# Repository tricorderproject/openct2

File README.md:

openct2
======

Open Source Computed Tomography (CT) Scanner v2 <br>
http://www.tricorderproject.org/openct <br>
Copyright (C) 2015  Peter Jansen and the Tricorder project <br>
peter@tricorderproject.org <br>
Project Build Logs: https://hackaday.io/project/5946-openct2 <br>

# Introduction

The Open Source Computed Tomography (CT) Scanner project aims to move towards creating an inexpensive and open desktop computed tomography scanner for academic and educational purposes.  The most common form of computed tomography is radiographic using x-rays or gamma rays, although it is my hope that this project can serve as a general platform for other kinds of tomographic research with other, safer wavelengths. 

This project is intended for use with radioisotope "check" sources that are many orders of magnitude less intense than sources in a commercial or medical radiographic setups.  This means that even very low resolution images will take hours of measurement and integration time to assemble, and the resolution and signal to noise ratio of a scan are largely a function of time (and patience).  Much of the spirit of this project is to move towards creating better scans through the use of clever signal processing techniques or wavelengths that can be more efficiently detected, rather than increasing source intensity. 

# Open Source

This project is open hardware and is released under various open licenses.  Please see LICENSES.TXT for details.

For potential contributors, a list of suggested contributions and next steps can be found in TODO.TXT .

# Warning

This project has a variety of dangers associated with it, including (without limitation) its assembly and use.  This generally includes the typical hazards involved with assembling, testing, and using electronics projects, CNC projects, as well as using hand tools, power tools, and CNC manufacturing tools such as laser cutters or CNC routers.  This is not a first project in any of these areas, and one should be well experienced and comfortable in all aspects of this project's design, assembly, and use. 

In addition, for radiography this project makes use of a low intensity sealed radioactive radioisotope source.  You should be experienced and extremely comfortable with handling and using radioactive sources, understanding the potential dangers (and how to minimize them), as well as any local laws or regulations regarding such material.  Having advanced training in medical imaging, radiography, and/or radiation biophysics is highly recommended.  

In no case should any living thing be placed inside of or be scanned by the device. 

**DISCLAIMER OF WARRANTIES AND LIMITATION OF LIABILITY.**

UNLESS OTHERWISE SEPARATELY UNDERTAKEN BY THE LICENSOR, TO THE EXTENT POSSIBLE, THE LICENSOR OFFERS THE LICENSED MATERIAL AS-IS AND AS-AVAILABLE, AND MAKES NO REPRESENTATIONS OR WARRANTIES OF ANY KIND CONCERNING THE LICENSED MATERIAL, WHETHER EXPRESS, IMPLIED, STATUTORY, OR OTHER. THIS INCLUDES, WITHOUT LIMITATION, WARRANTIES OF TITLE, MERCHANTABILITY, FITNESS FOR A PARTICULAR PURPOSE, NON-INFRINGEMENT, ABSENCE OF LATENT OR OTHER DEFECTS, ACCURACY, OR THE PRESENCE OR ABSENCE OF ERRORS, WHETHER OR NOT KNOWN OR DISCOVERABLE. WHERE DISCLAIMERS OF WARRANTIES ARE NOT ALLOWED IN FULL OR IN PART, THIS DISCLAIMER MAY NOT APPLY TO YOU.

TO THE EXTENT POSSIBLE, IN NO EVENT WILL THE LICENSOR BE LIABLE TO YOU ON ANY LEGAL THEORY (INCLUDING, WITHOUT LIMITATION, NEGLIGENCE) OR OTHERWISE FOR ANY DIRECT, SPECIAL, INDIRECT, INCIDENTAL, CONSEQUENTIAL, PUNITIVE, EXEMPLARY, OR OTHER LOSSES, COSTS, EXPENSES, OR DAMAGES ARISING OUT OF THIS PUBLIC LICENSE OR USE OF THE LICENSED MATERIAL, EVEN IF THE LICENSOR HAS BEEN ADVISED OF THE POSSIBILITY OF SUCH LOSSES, COSTS, EXPENSES, OR DAMAGES. WHERE A LIMITATION OF LIABILITY IS NOT ALLOWED IN FULL OR IN PART, THIS LIMITATION MAY NOT APPLY TO YOU.

THE DISCLAIMER OF WARRANTIES AND LIMITATION OF LIABILITY PROVIDED ABOVE SHALL BE INTERPRETED IN A MANNER THAT, TO THE EXTENT POSSIBLE, MOST CLOSELY APPROXIMATES AN ABSOLUTE DISCLAIMER AND WAIVER OF ALL LIABILITY.

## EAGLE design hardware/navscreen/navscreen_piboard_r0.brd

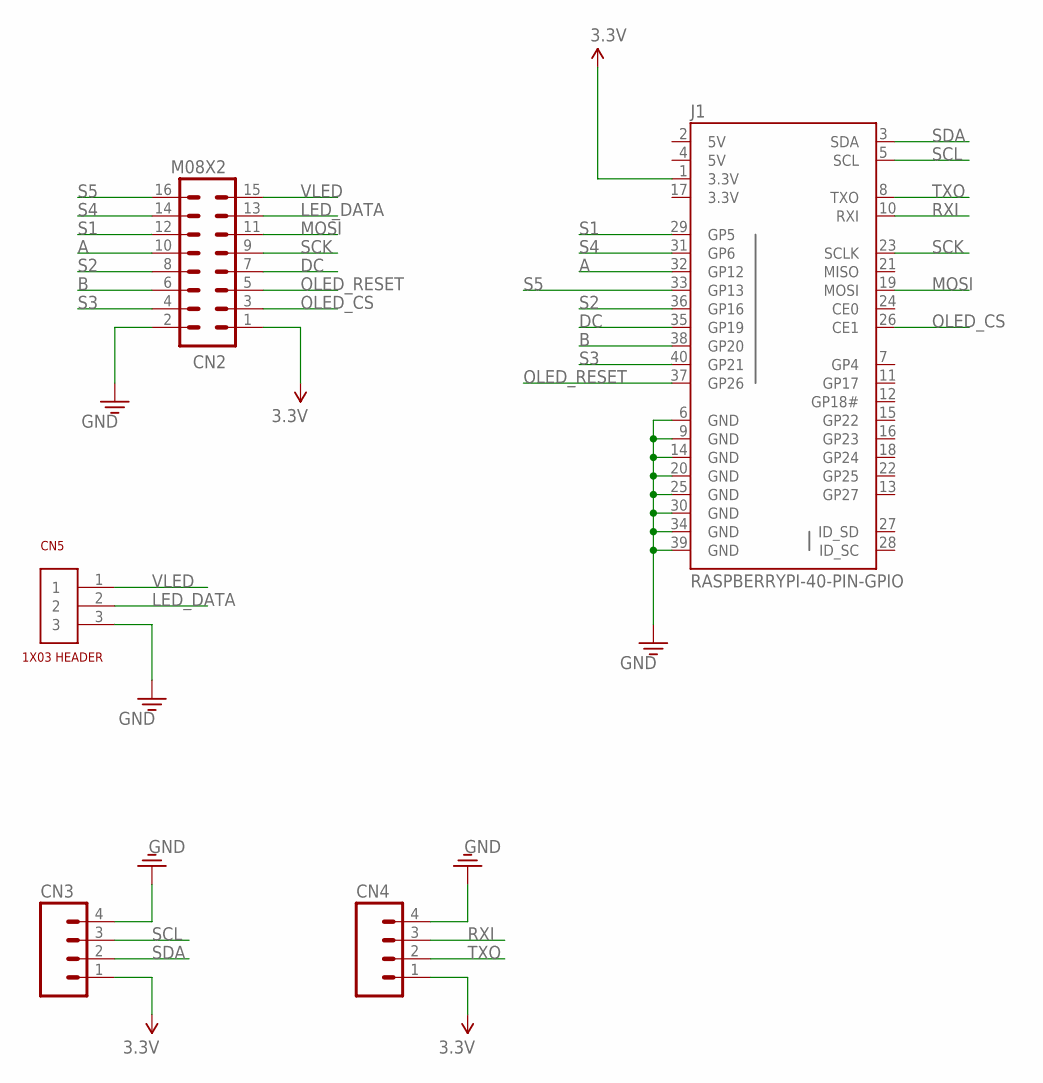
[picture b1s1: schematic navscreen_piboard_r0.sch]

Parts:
CN2: M08X2; 2X8
CN3, CN4: M04PTH; 1X04
CN5: 1X03
J1: RASPBERRYPI-40-PIN-GPIO; 2X20-SHROUDED

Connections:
3.3V: CN2.1, CN3.1, CN4.1, J1.1 (3.3V), J1.17 (3.3V)
A: CN2.10, J1.32 (GP12)
B: CN2.6, J1.38 (GP20)
DC: CN2.7, J1.35 (GP19)
GND: CN2.2, CN3.4, CN4.4, CN5.3, J1.6 (GND), J1.9 (GND), J1.14 (GND), J1.20 (GND), J1.25 (GND), J1.30 (GND), J1.34 (GND), J1.39 (GND)
LED_DATA: CN2.13, CN5.2
MOSI: CN2.11, J1.19 (MOSI)
OLED_CS: CN2.3, J1.26 (CE1)
OLED_RESET: CN2.5, J1.37 (GP26)
RXI: CN4.3, J1.10 (RXI)
S1: CN2.12, J1.29 (GP5)
S2: CN2.8, J1.36 (GP16)
S3: CN2.4, J1.40 (GP21)
S4: CN2.14, J1.31 (GP6)
S5: CN2.16, J1.33 (GP13)
SCK: CN2.9, J1.23 (SCLK)
SCL: CN3.3, J1.5 (SCL)
SDA: CN3.2, J1.3 (SDA)
TXO: CN4.2, J1.8 (TXO)
VLED: CN2.15, CN5.1, J1.2 (5V), J1.4 (5V)

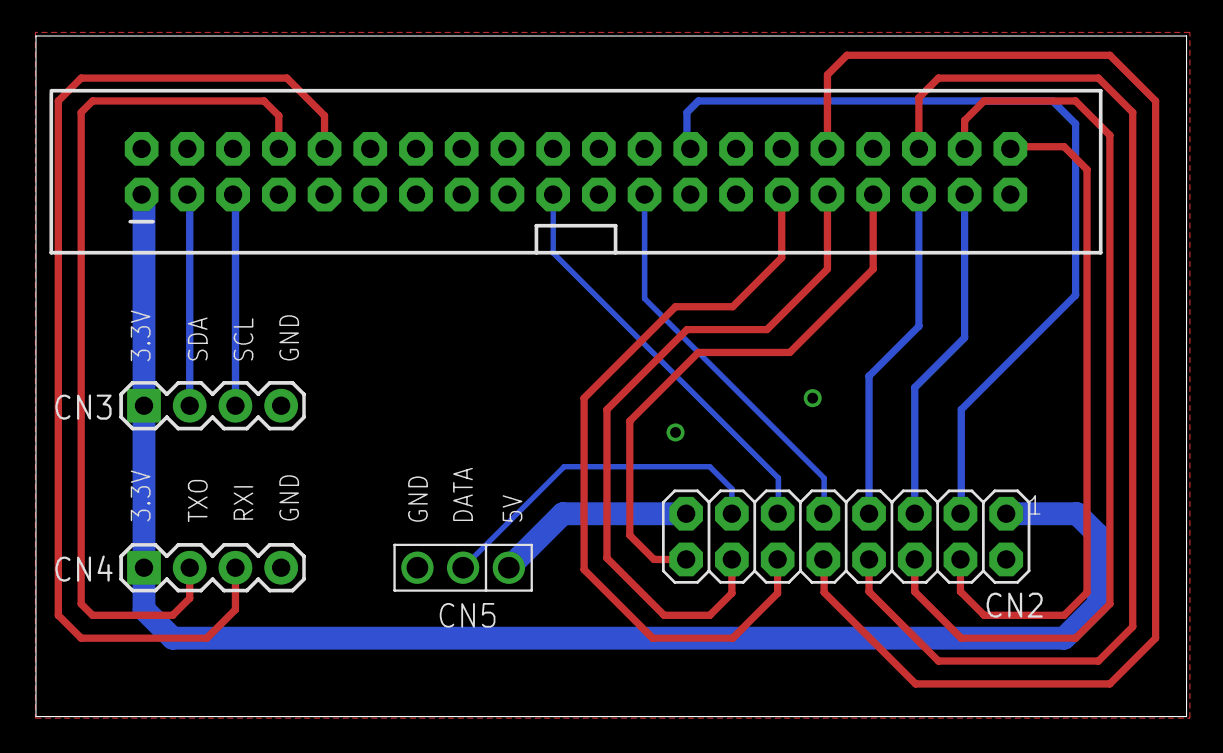
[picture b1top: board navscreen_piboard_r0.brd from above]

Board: 2 copper layers, 63.9 x 37.8 mm, 5 parts (0 on the bottom side), 20 nets.

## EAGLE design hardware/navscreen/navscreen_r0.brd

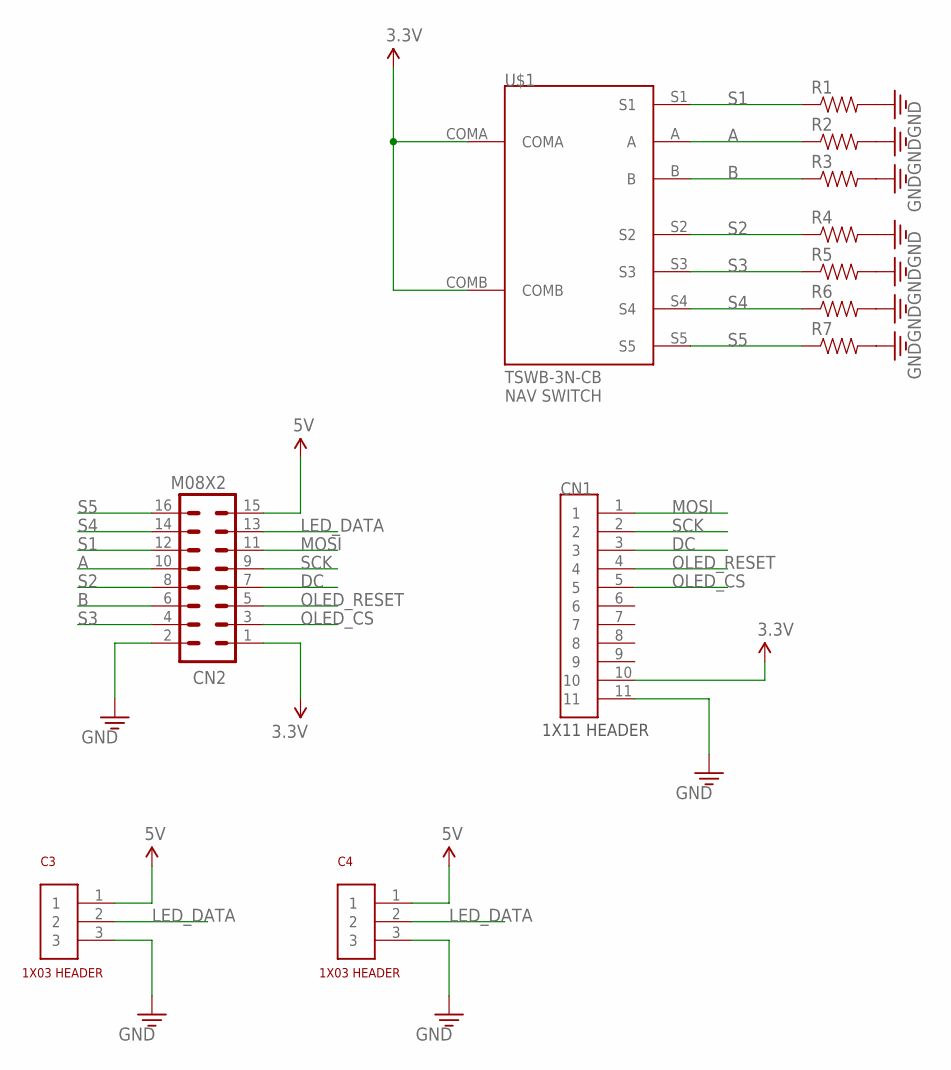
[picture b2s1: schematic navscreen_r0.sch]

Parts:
C3, C4: 1X03
CN1: 1X11
CN2: M08X2; 2X8
R1, R2, R3, R4, R5, R6, R7: RESISTOR0603; 0603
U$1: NAV-SWITCH-TSWB-3N-CB; TSWB-3N-CB

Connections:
3.3V: CN1.10, CN2.1, U$1.COMA, U$1.COMB
5V: C3.1, C4.1, CN2.15
A: CN2.10, R2.1, U$1.A
B: CN2.6, R3.1, U$1.B
DC: CN1.3, CN2.7
GND: C3.3, C4.3, CN1.11, CN2.2, R1.2, R2.2, R3.2, R4.2, R5.2, R6.2, R7.2
LED_DATA: C3.2, C4.2, CN2.13
MOSI: CN1.1, CN2.11
OLED_CS: CN1.5, CN2.3
OLED_RESET: CN1.4, CN2.5
S1: CN2.12, R1.1, U$1.S1
S2: CN2.8, R4.1, U$1.S2
S3: CN2.4, R5.1, U$1.S3
S4: CN2.14, R6.1, U$1.S4
S5: CN2.16, R7.1, U$1.S5
SCK: CN1.2, CN2.9

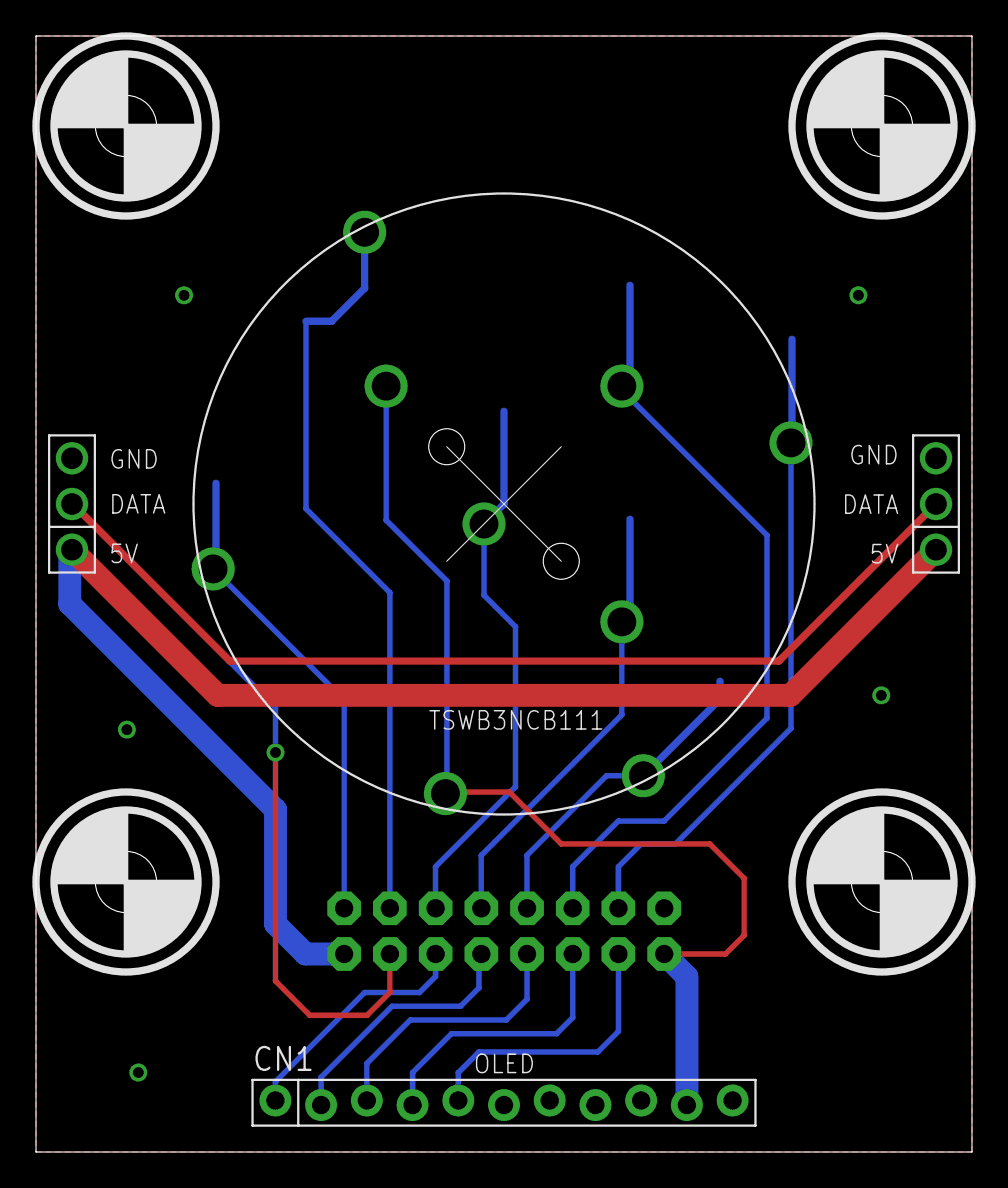
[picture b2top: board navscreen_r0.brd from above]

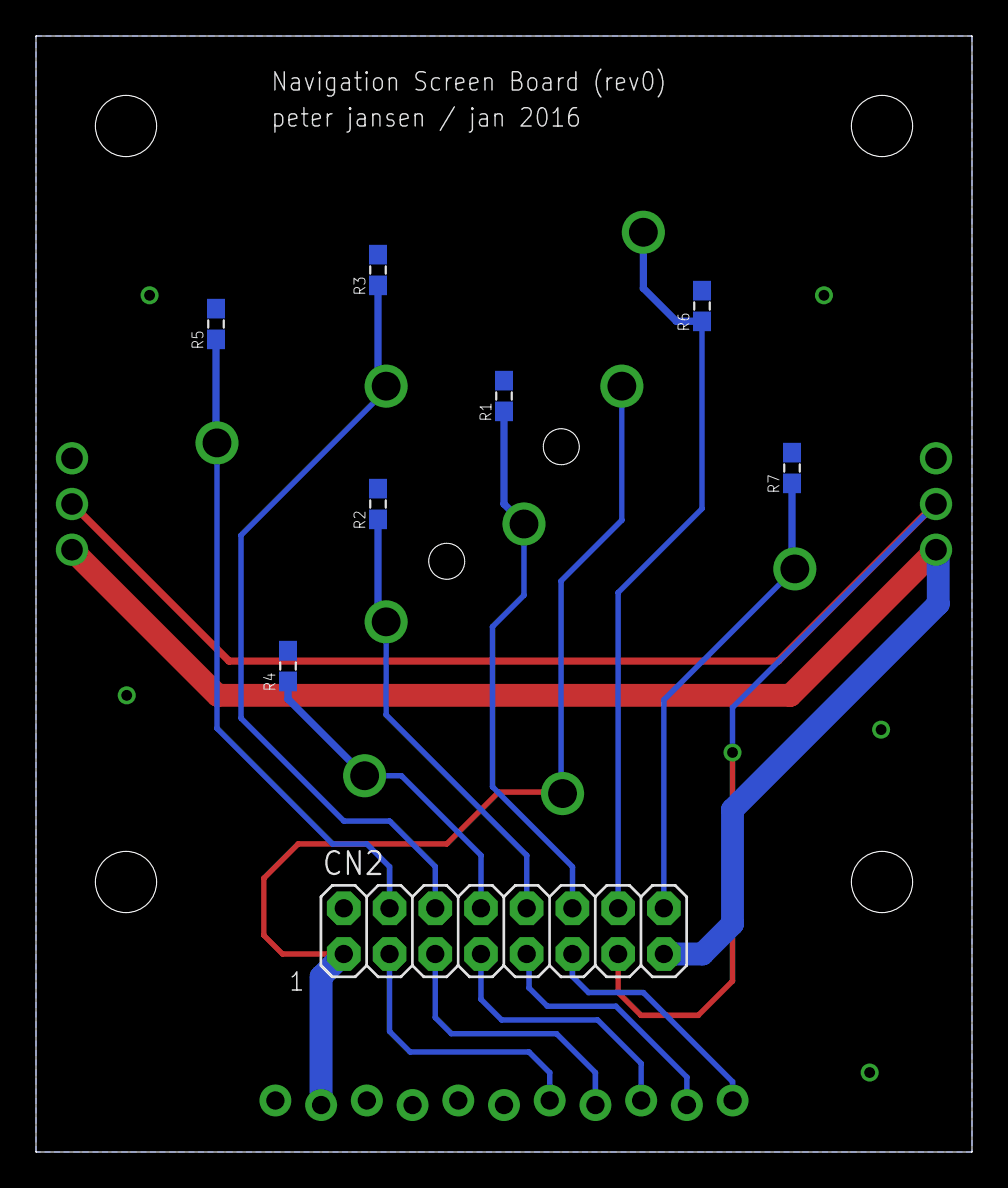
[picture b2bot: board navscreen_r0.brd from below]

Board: 2 copper layers, 52.0 x 62.0 mm, 12 parts (8 on the bottom side), 16 nets.

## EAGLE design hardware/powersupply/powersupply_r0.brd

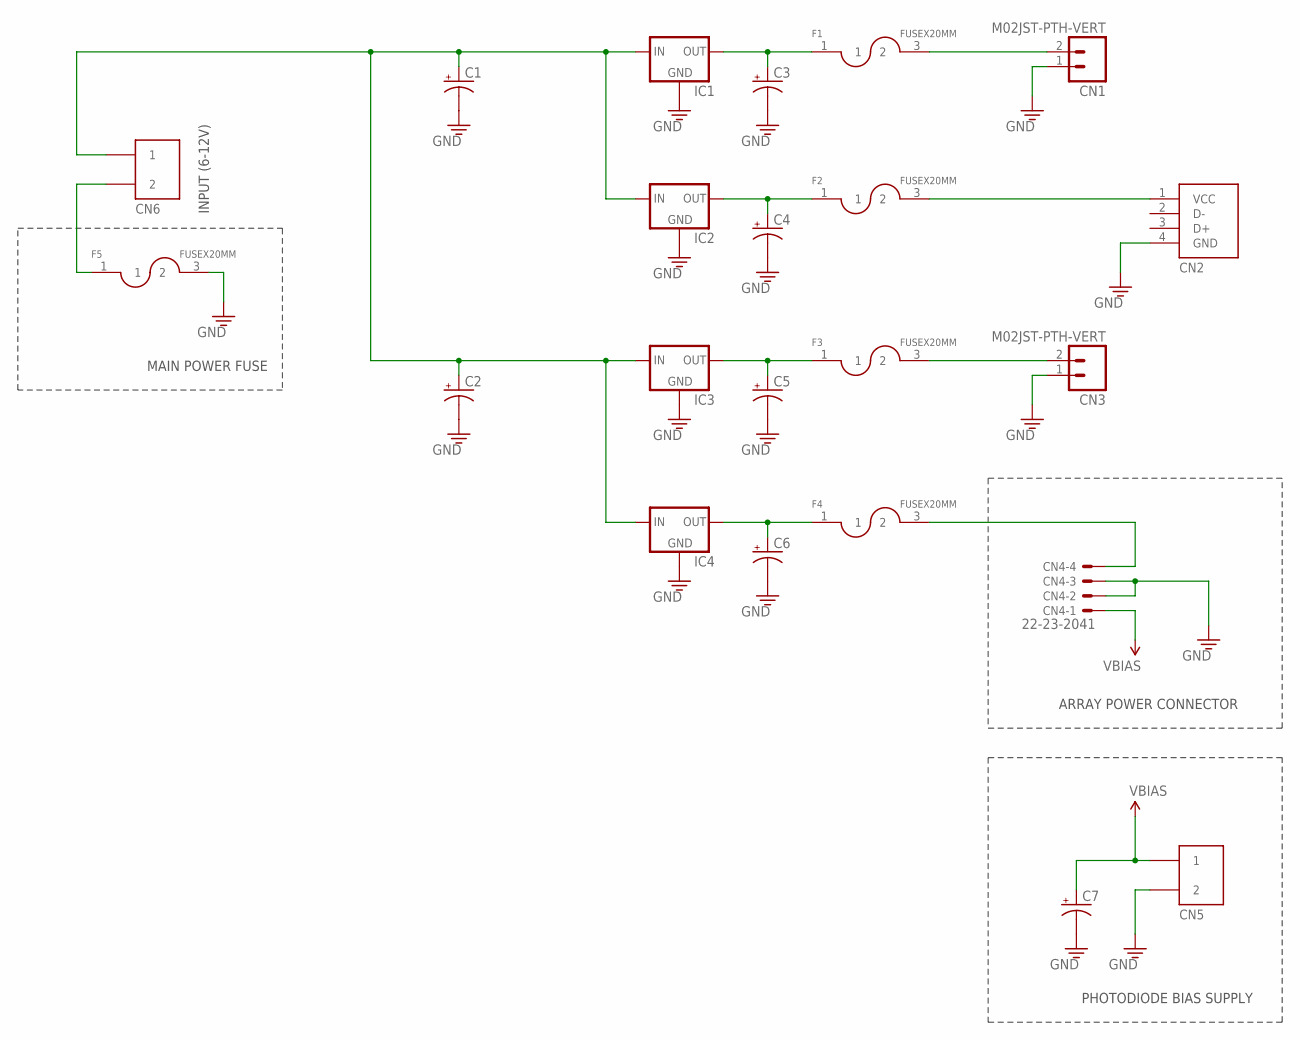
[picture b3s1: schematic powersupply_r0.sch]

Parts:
C1, C2: CAP_POLPTH4; CPOL-RADIAL-1000UF-25V
C3, C4, C5, C6, C7: CAP_POLPTH1; CPOL-RADIAL-100UF-25V
CN1, CN3: M02JST-PTH-VERT; JST-2-PTH-VERT
CN2: CON-USB; MOLEX-USB-105057-0001
CN4: 22-23-2041
CN5, CN6: SCREWTERMINAL-2PIN
F1, F2, F3, F4, F5: FUSEX20MM; FUSE_5MM
IC1, IC2, IC3, IC4: V_REG_78XXSINK; TO220-IGO

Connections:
GND: C1.2 (-), C2.2 (-), C3.2 (-), C4.2 (-), C5.2 (-), C6.2 (-), C7.2 (-), CN1.1 (2), CN2.4 (GND), CN3.1 (2), CN4.2, CN4.3, CN5.2, F5.3 (2), IC1.GND, IC2.GND, IC3.GND, IC4.GND
unnamed: C3.1 (+), F1.1, IC1.OUT
unnamed: C4.1 (+), F2.1, IC2.OUT
unnamed: C5.1 (+), F3.1, IC3.OUT
unnamed: C6.1 (+), F4.1, IC4.OUT
unnamed: CN4.4, F4.3 (2)
unnamed: CN6.2, F5.1
unnamed: CN1.2 (1), F1.3 (2)
unnamed: CN2.1 (VCC), F2.3 (2)
unnamed: CN3.2 (1), F3.3 (2)
unnamed: C1.1 (+), C2.1 (+), CN6.1, IC1.IN, IC2.IN, IC3.IN, IC4.IN
VBIAS: C7.1 (+), CN4.1, CN5.1

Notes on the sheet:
ARRAY POWER CONNECTOR
MAIN POWER FUSE
INPUT (6-12V)
PHOTODIODE BIAS SUPPLY

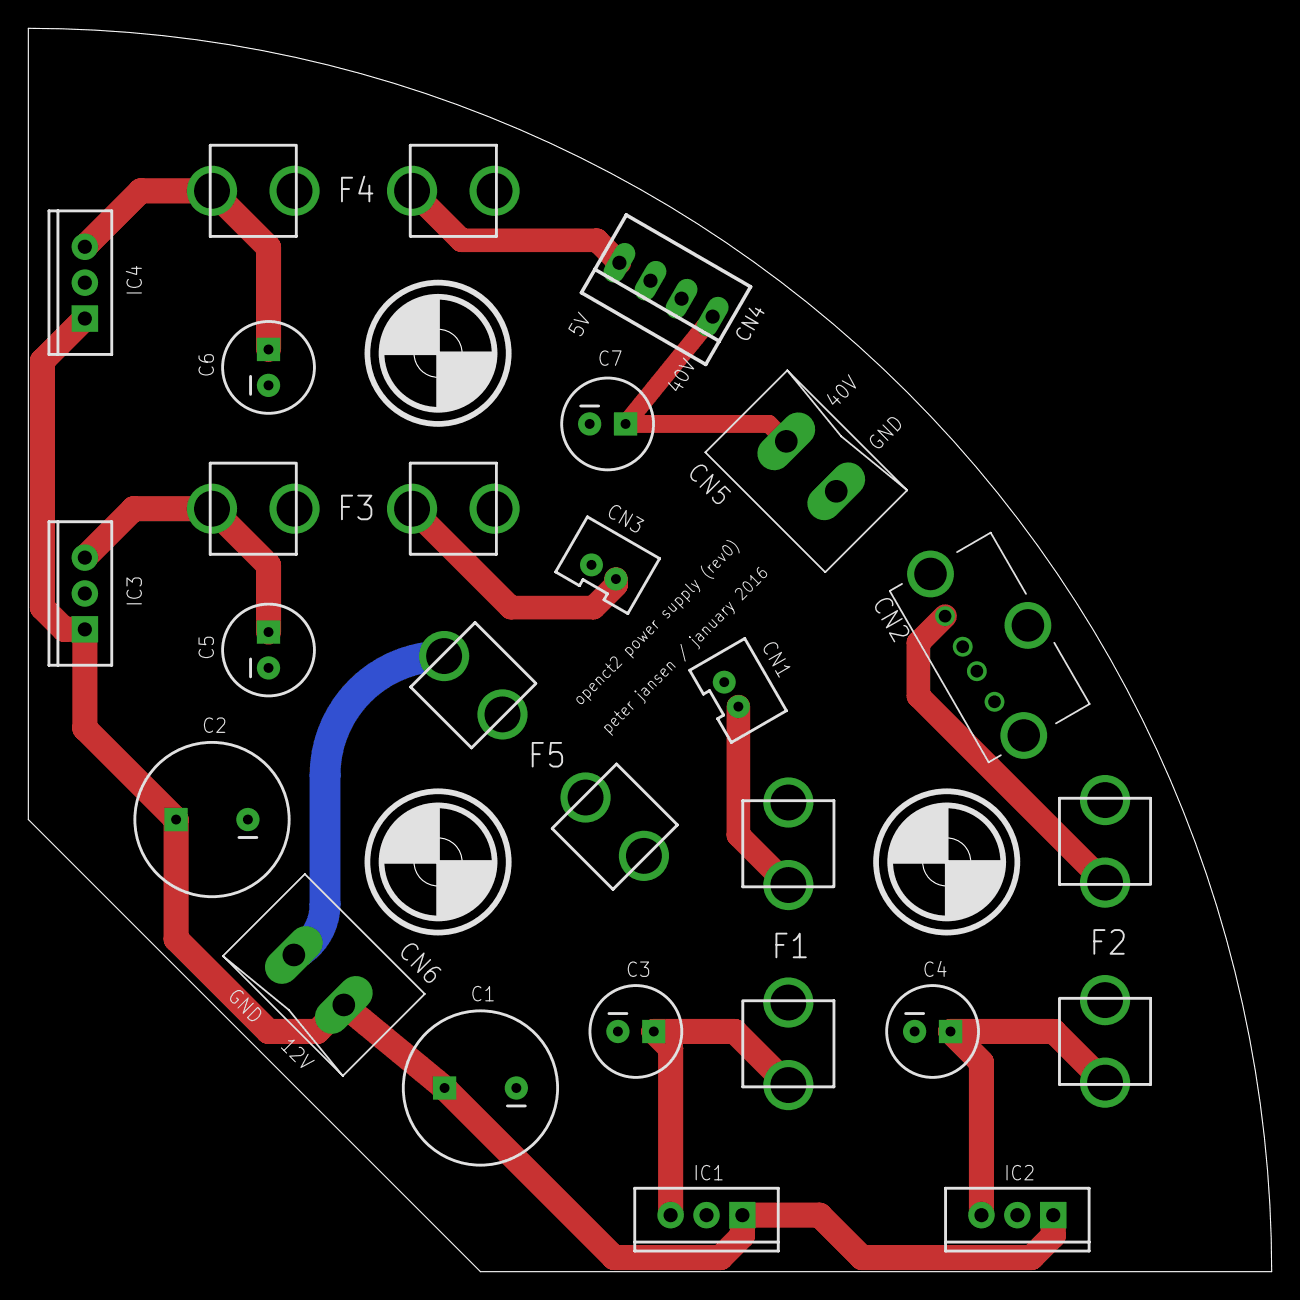
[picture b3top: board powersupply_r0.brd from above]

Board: 2 copper layers, 88.0 x 88.0 mm, 22 parts (0 on the bottom side), 12 nets.

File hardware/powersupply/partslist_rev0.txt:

CN1, CN3	JST Connector	B2B-PH-K-S(LF)(SN)
+ Cables (from Sparkfun?)

CN2		USB Connector	Molex 105057-0001		

CN4		Imaging Array Connector		A33896-ND

CN5, CN6	5mm pitch Screw Terminals			TODO

C3-C6		Capacitors	5mm dia, 47uF, 16V	(ECA-1EHG470)
C7		Capacitor	5mm dia, 100V		(ECA-2AM100)
C1-C2		Capacitors	10mm dia, 25V 		(ECA-1VM471)


IC1-4		2A Linear Regulators	L78S05CV-DG

F1-5		20mm/5mm Fuse Clips (qty 10)

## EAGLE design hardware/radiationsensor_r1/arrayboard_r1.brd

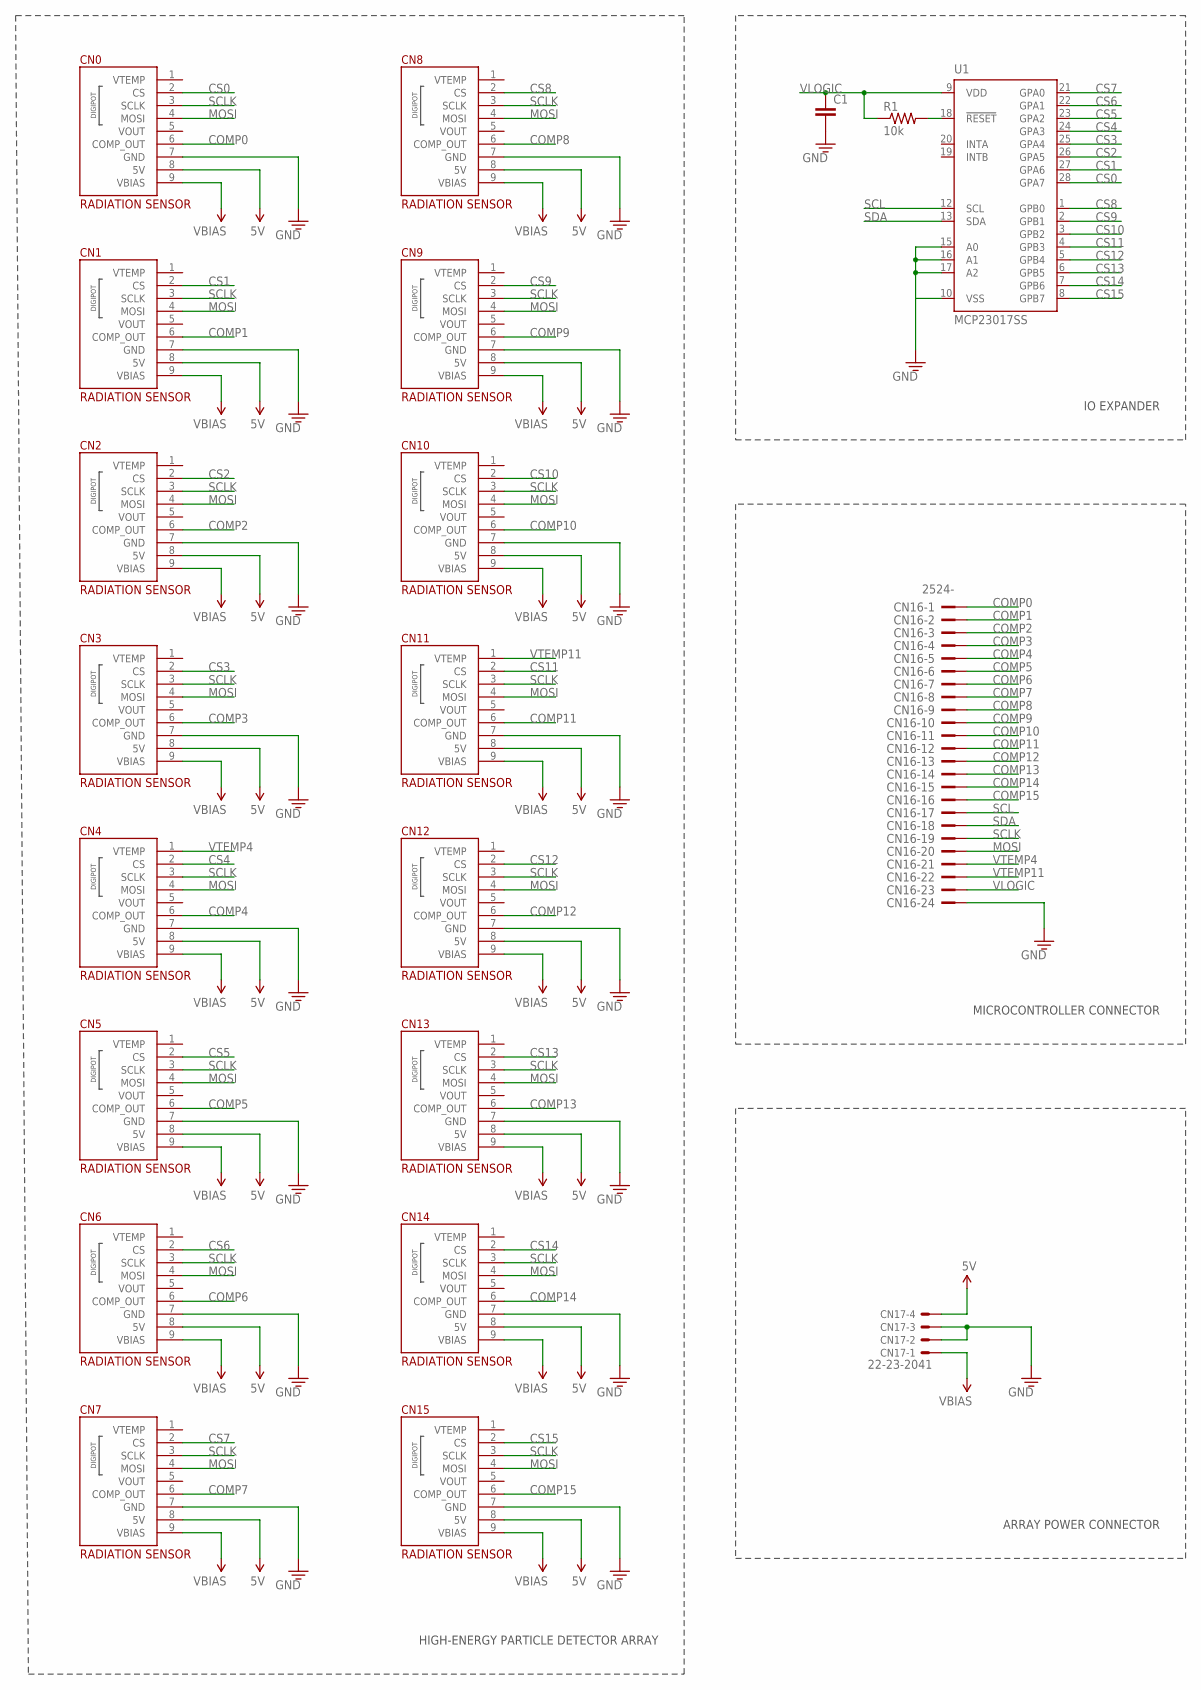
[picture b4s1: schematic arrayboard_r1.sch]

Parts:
C1: CAP0603; 0603
CN0, CN1, CN2, CN3, CN4, CN5, CN6, CN7, CN8, CN9, CN10, CN11, CN12, CN13, CN14, CN15: RADIATION-SENSOR-REV1
CN16: 2524-; PAK100/2500-24
CN17: 22-23-2041
R1: 10k; 0603
U1: MCP23017SS; SSOP28

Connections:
5V: CN0.8 (5V), CN1.8 (5V), CN2.8 (5V), CN3.8 (5V), CN4.8 (5V), CN5.8 (5V), CN6.8 (5V), CN7.8 (5V), CN8.8 (5V), CN9.8 (5V), CN10.8 (5V), CN11.8 (5V), CN12.8 (5V), CN13.8 (5V), CN14.8 (5V), CN15.8 (5V), CN17.4
COMP0: CN0.6 (COMP_OUT), CN16.1
COMP1: CN1.6 (COMP_OUT), CN16.2
COMP2: CN2.6 (COMP_OUT), CN16.3
COMP3: CN3.6 (COMP_OUT), CN16.4
COMP4: CN4.6 (COMP_OUT), CN16.5
COMP5: CN5.6 (COMP_OUT), CN16.6
COMP6: CN6.6 (COMP_OUT), CN16.7
COMP7: CN7.6 (COMP_OUT), CN16.8
COMP8: CN8.6 (COMP_OUT), CN16.9
COMP9: CN9.6 (COMP_OUT), CN16.10
COMP10: CN10.6 (COMP_OUT), CN16.11
COMP11: CN11.6 (COMP_OUT), CN16.12
COMP12: CN12.6 (COMP_OUT), CN16.13
COMP13: CN13.6 (COMP_OUT), CN16.14
COMP14: CN14.6 (COMP_OUT), CN16.15
COMP15: CN15.6 (COMP_OUT), CN16.16
CS0: CN0.2 (CS), U1.28 (GPA7)
CS1: CN1.2 (CS), U1.27 (GPA6)
CS2: CN2.2 (CS), U1.26 (GPA5)
CS3: CN3.2 (CS), U1.25 (GPA4)
CS4: CN4.2 (CS), U1.24 (GPA3)
CS5: CN5.2 (CS), U1.23 (GPA2)
CS6: CN6.2 (CS), U1.22 (GPA1)
CS7: CN7.2 (CS), U1.21 (GPA0)
CS8: CN8.2 (CS), U1.1 (GPB0)
CS9: CN9.2 (CS), U1.2 (GPB1)
CS10: CN10.2 (CS), U1.3 (GPB2)
CS11: CN11.2 (CS), U1.4 (GPB3)
CS12: CN12.2 (CS), U1.5 (GPB4)
CS13: CN13.2 (CS), U1.6 (GPB5)
CS14: CN14.2 (CS), U1.7 (GPB6)
CS15: CN15.2 (CS), U1.8 (GPB7)
GND: C1.2, CN0.7 (GND), CN1.7 (GND), CN2.7 (GND), CN3.7 (GND), CN4.7 (GND), CN5.7 (GND), CN6.7 (GND), CN7.7 (GND), CN8.7 (GND), CN9.7 (GND), CN10.7 (GND), CN11.7 (GND), CN12.7 (GND), CN13.7 (GND), CN14.7 (GND), CN15.7 (GND), CN16.24, CN17.2, CN17.3, U1.10 (VSS), U1.15 (A0), U1.16 (A1), U1.17 (A2)
MOSI: CN0.4 (MOSI), CN1.4 (MOSI), CN2.4 (MOSI), CN3.4 (MOSI), CN4.4 (MOSI), CN5.4 (MOSI), CN6.4 (MOSI), CN7.4 (MOSI), CN8.4 (MOSI), CN9.4 (MOSI), CN10.4 (MOSI), CN11.4 (MOSI), CN12.4 (MOSI), CN13.4 (MOSI), CN14.4 (MOSI), CN15.4 (MOSI), CN16.20
unnamed: R1.2, U1.18 (!RESET)
SCL: CN16.17, U1.12 (SCL)
SCLK: CN0.3 (SCLK), CN1.3 (SCLK), CN2.3 (SCLK), CN3.3 (SCLK), CN4.3 (SCLK), CN5.3 (SCLK), CN6.3 (SCLK), CN7.3 (SCLK), CN8.3 (SCLK), CN9.3 (SCLK), CN10.3 (SCLK), CN11.3 (SCLK), CN12.3 (SCLK), CN13.3 (SCLK), CN14.3 (SCLK), CN15.3 (SCLK), CN16.19
SDA: CN16.18, U1.13 (SDA)
VBIAS: CN0.9 (VBIAS), CN1.9 (VBIAS), CN2.9 (VBIAS), CN3.9 (VBIAS), CN4.9 (VBIAS), CN5.9 (VBIAS), CN6.9 (VBIAS), CN7.9 (VBIAS), CN8.9 (VBIAS), CN9.9 (VBIAS), CN10.9 (VBIAS), CN11.9 (VBIAS), CN12.9 (VBIAS), CN13.9 (VBIAS), CN14.9 (VBIAS), CN15.9 (VBIAS), CN17.1
VLOGIC: C1.1, CN16.23, R1.1, U1.9 (VDD)
VTEMP4: CN4.1 (VTEMP), CN16.21
VTEMP11: CN11.1 (VTEMP), CN16.22

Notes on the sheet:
HIGH-ENERGY PARTICLE DETECTOR ARRAY
ARRAY POWER CONNECTOR
MICROCONTROLLER CONNECTOR
IO EXPANDER

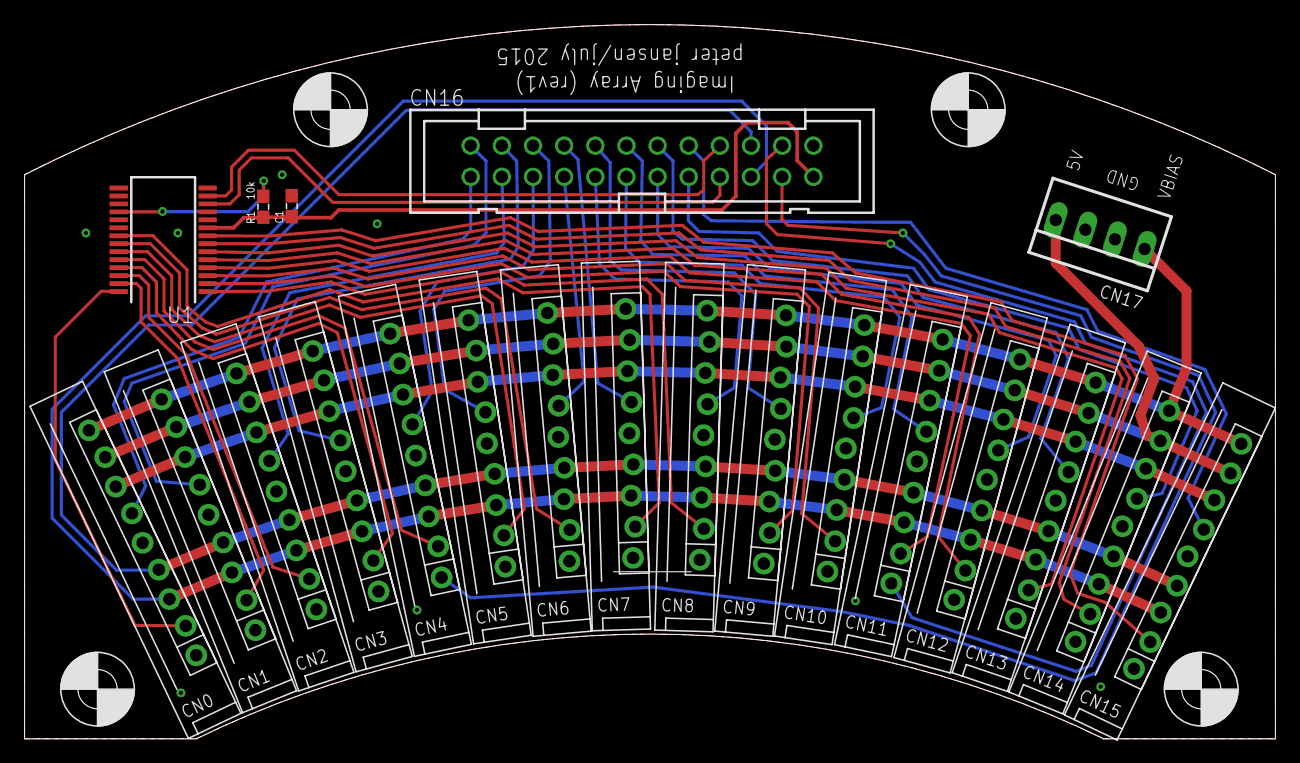
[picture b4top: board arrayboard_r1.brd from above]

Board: 2 copper layers, 102.0 x 58.2 mm, 25 parts (0 on the bottom side), 43 nets.

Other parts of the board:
U$35, U$36, U$37, U$38: MOUNT-M3

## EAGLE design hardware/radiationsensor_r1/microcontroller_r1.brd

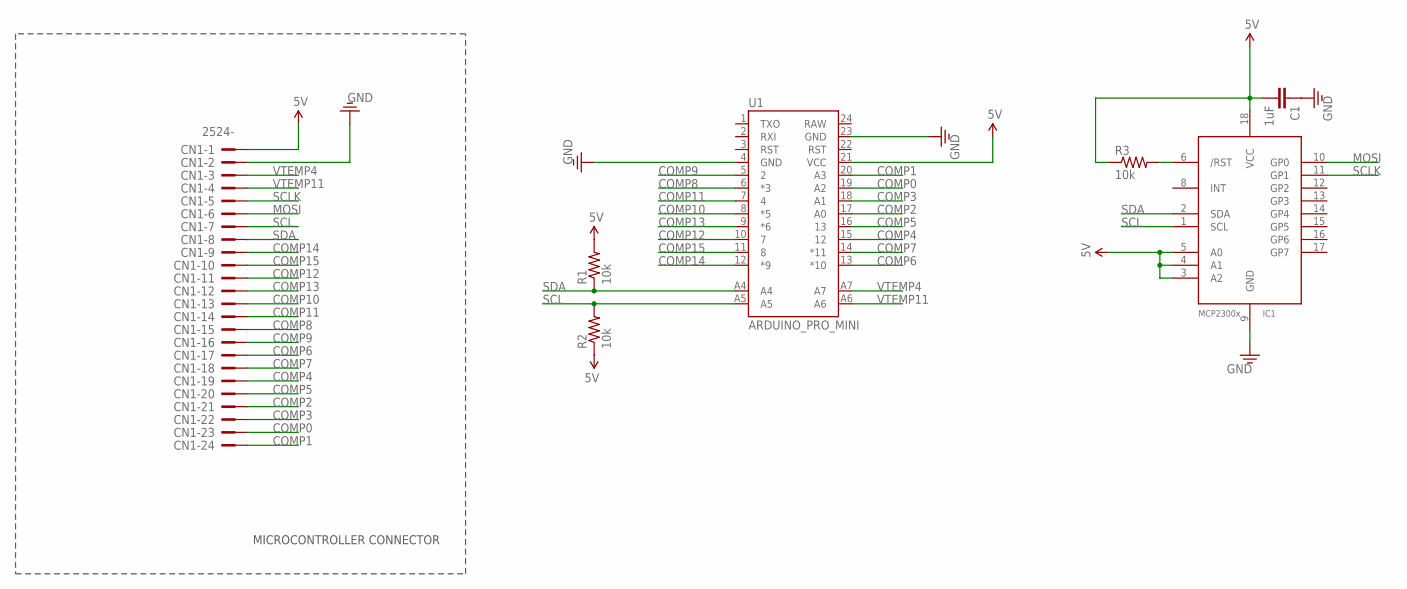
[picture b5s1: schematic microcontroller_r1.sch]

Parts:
C1: 1uF; 0603
CN1: 2524-; PAK100/2500-24
IC1: MCP2300X/SO; SO18W
R1, R2, R3: 10k; 0603
U1: ARDUINO_PRO_MINI

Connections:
5V: C1.2, CN1.1, IC1.3 (A2), IC1.4 (A1), IC1.5 (A0), IC1.18 (VCC), R1.2, R2.1, R3.1, U1.21 (VCC)
COMP0: CN1.23, U1.19 (A2)
COMP1: CN1.24, U1.20 (A3)
COMP2: CN1.21, U1.17 (A0)
COMP3: CN1.22, U1.18 (A1)
COMP4: CN1.19, U1.15 (12)
COMP5: CN1.20, U1.16 (13)
COMP6: CN1.17, U1.13 (*10)
COMP7: CN1.18, U1.14 (*11)
COMP8: CN1.15, U1.6 (*3)
COMP9: CN1.16, U1.5 (2)
COMP10: CN1.13, U1.8 (*5)
COMP11: CN1.14, U1.7 (4)
COMP12: CN1.11, U1.10 (7)
COMP13: CN1.12, U1.9 (*6)
COMP14: CN1.9, U1.12 (*9)
COMP15: CN1.10, U1.11 (8)
GND: C1.1, CN1.2, IC1.9 (GND), U1.4 (GND), U1.23 (GND)
MOSI: CN1.6, IC1.10 (GP0)
unnamed: IC1.6 (/RST), R3.2
SCL: CN1.7, IC1.1 (SCL), R2.2, U1.A5
SCLK: CN1.5, IC1.11 (GP1)
SDA: CN1.8, IC1.2 (SDA), R1.1, U1.A4
VTEMP4: CN1.3, U1.A7
VTEMP11: CN1.4, U1.A6

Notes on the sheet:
MICROCONTROLLER CONNECTOR

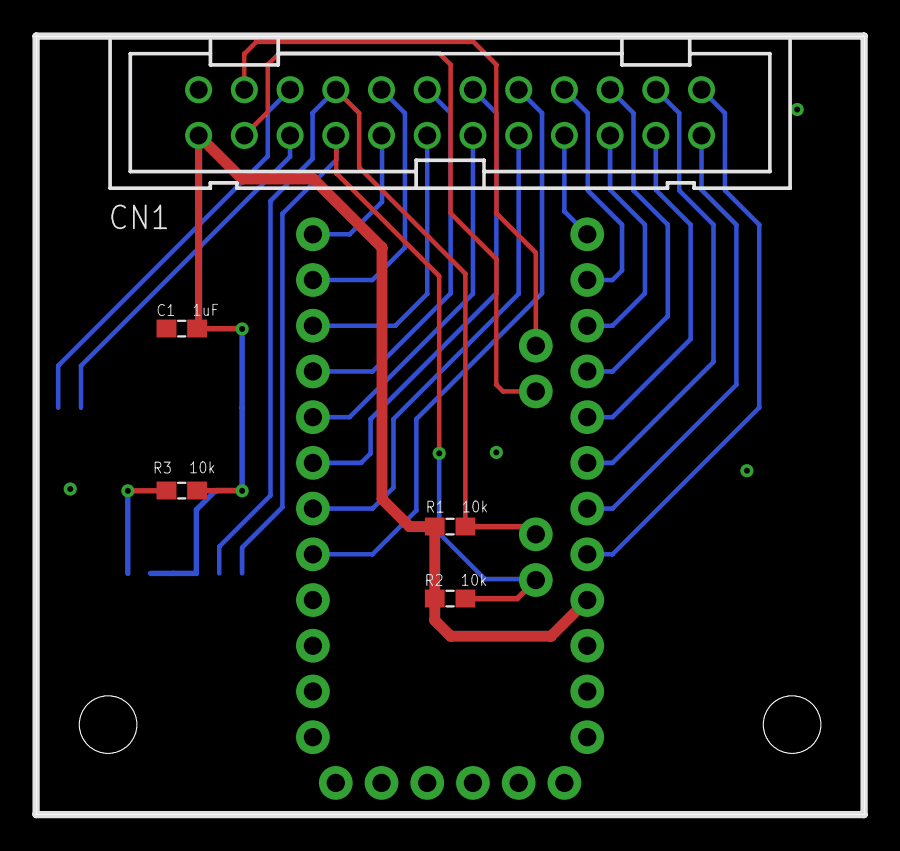
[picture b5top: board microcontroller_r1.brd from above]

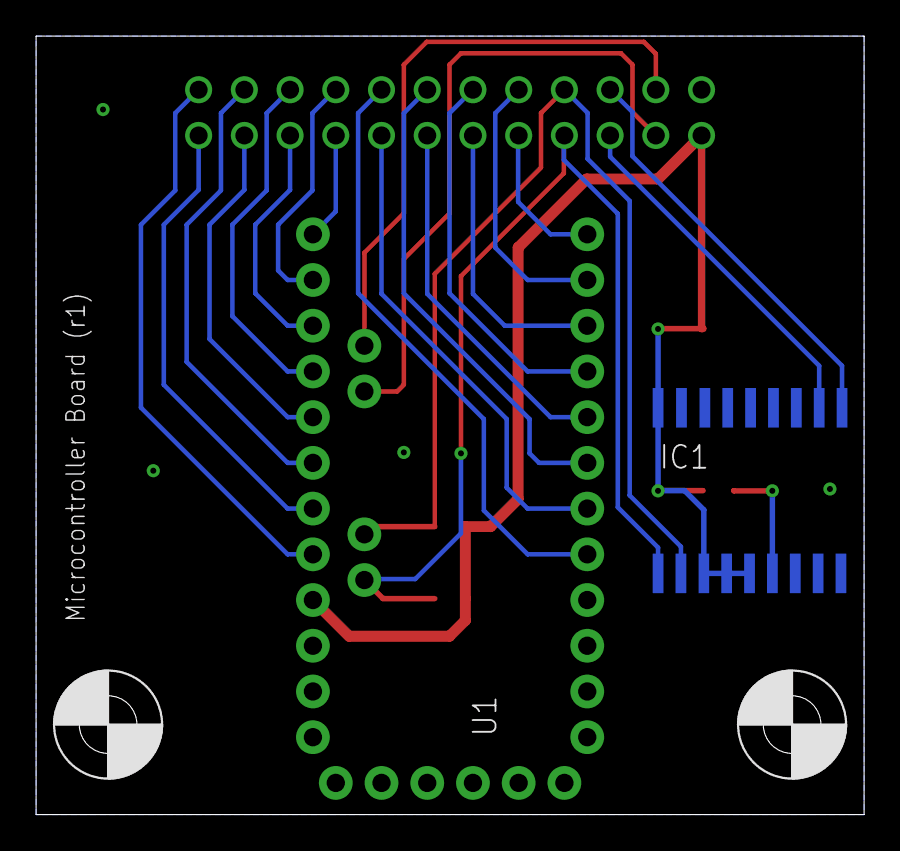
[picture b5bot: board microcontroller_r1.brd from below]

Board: 2 copper layers, 46.0 x 43.2 mm, 9 parts (4 on the bottom side), 25 nets.

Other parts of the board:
U$35, U$36: MOUNT-M3

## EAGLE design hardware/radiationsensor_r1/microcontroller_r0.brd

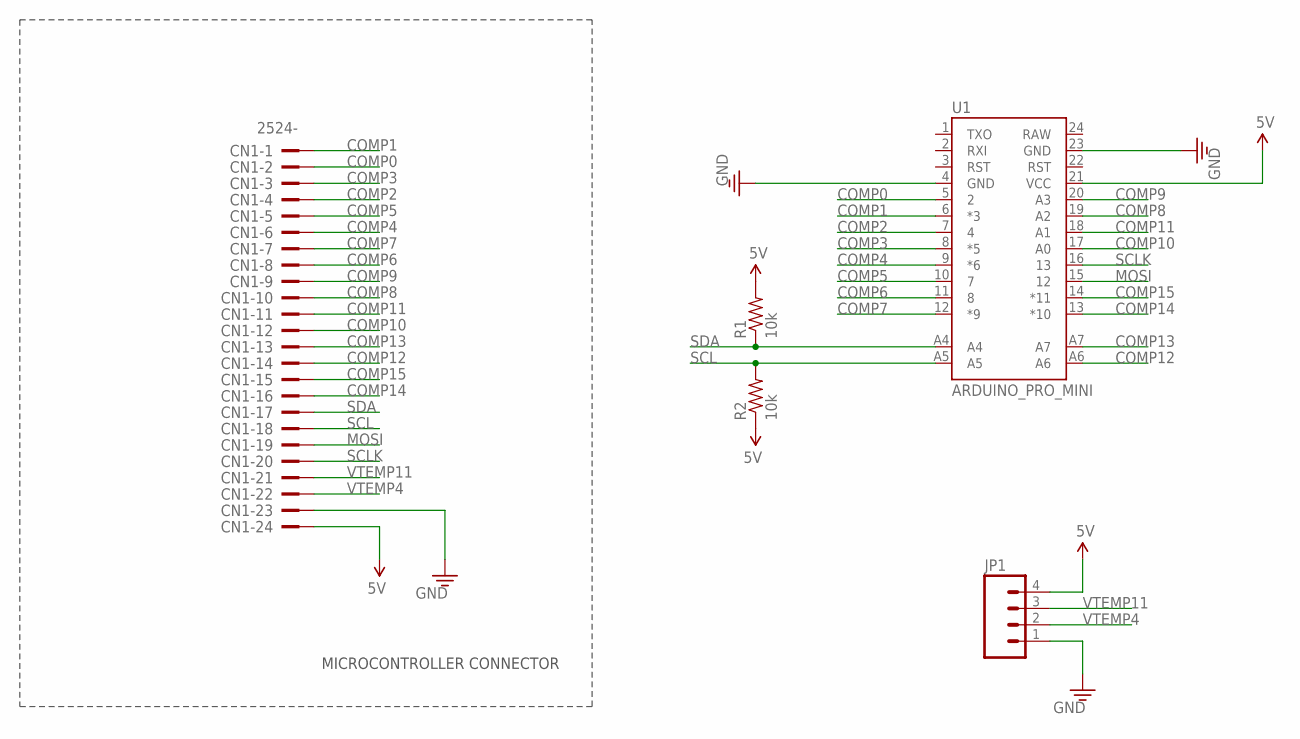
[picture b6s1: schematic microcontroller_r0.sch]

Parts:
CN1: 2524-; PAK100/2500-24
JP1: M04LOCK; 1X04_LOCK
R1, R2: 10k; 0603
U1: ARDUINO_PRO_MINI

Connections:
5V: CN1.24, JP1.4, R1.2, R2.1, U1.21 (VCC)
COMP0: CN1.2, U1.5 (2)
COMP1: CN1.1, U1.6 (*3)
COMP2: CN1.4, U1.7 (4)
COMP3: CN1.3, U1.8 (*5)
COMP4: CN1.6, U1.9 (*6)
COMP5: CN1.5, U1.10 (7)
COMP6: CN1.8, U1.11 (8)
COMP7: CN1.7, U1.12 (*9)
COMP8: CN1.10, U1.19 (A2)
COMP9: CN1.9, U1.20 (A3)
COMP10: CN1.12, U1.17 (A0)
COMP11: CN1.11, U1.18 (A1)
COMP12: CN1.14, U1.A6
COMP13: CN1.13, U1.A7
COMP14: CN1.16, U1.13 (*10)
COMP15: CN1.15, U1.14 (*11)
GND: CN1.23, JP1.1, U1.4 (GND), U1.23 (GND)
MOSI: CN1.19, U1.15 (12)
SCL: CN1.18, R2.2, U1.A5
SCLK: CN1.20, U1.16 (13)
SDA: CN1.17, R1.1, U1.A4
VTEMP4: CN1.22, JP1.2
VTEMP11: CN1.21, JP1.3

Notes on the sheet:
MICROCONTROLLER CONNECTOR

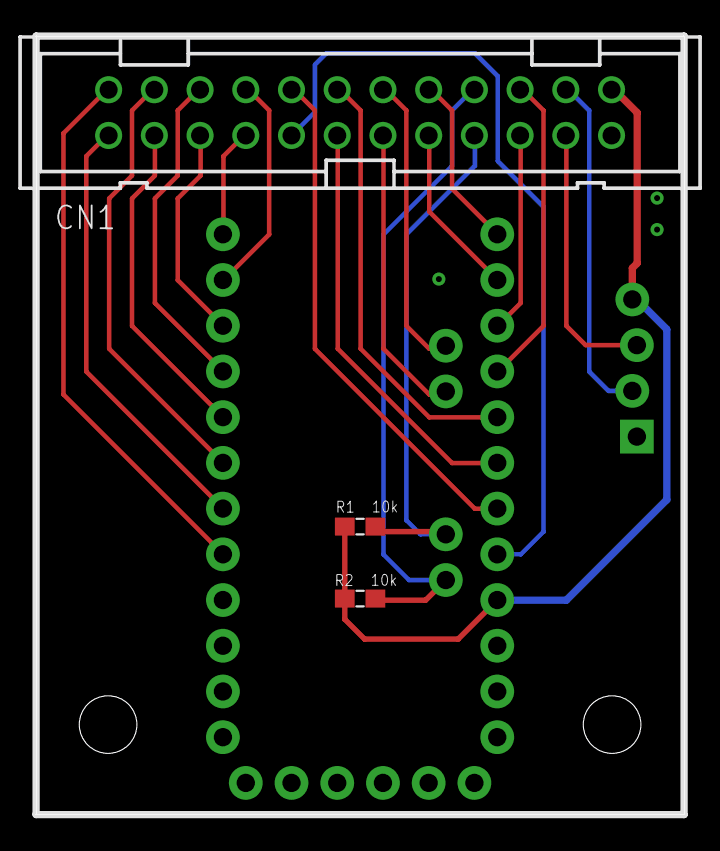
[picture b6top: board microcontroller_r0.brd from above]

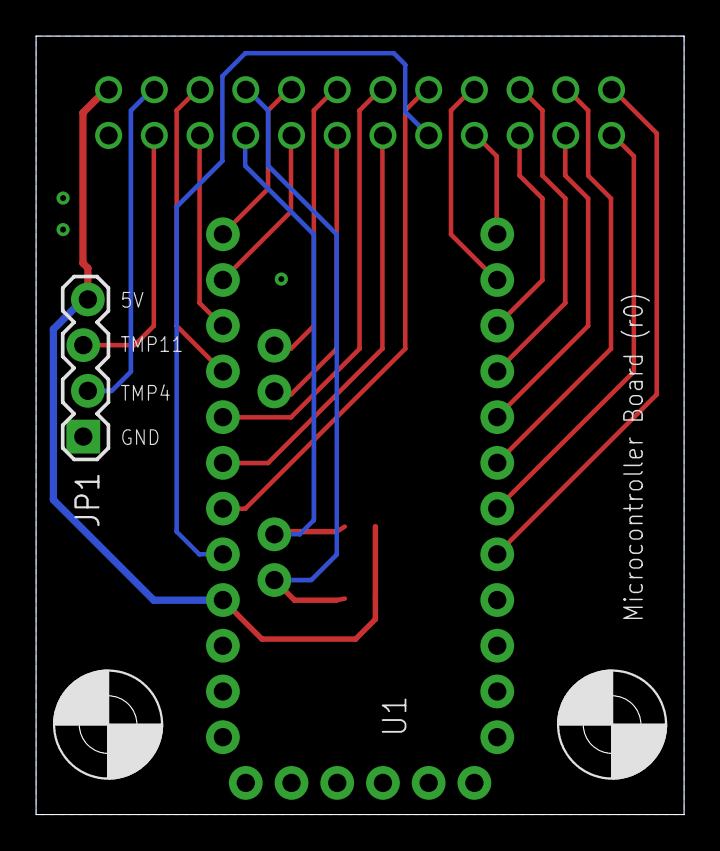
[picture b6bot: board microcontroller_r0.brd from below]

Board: 2 copper layers, 36.0 x 43.2 mm, 7 parts (4 on the bottom side), 24 nets.

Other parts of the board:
U$35, U$36: MOUNT-M3

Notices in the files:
parts and their libraries:
openct: Licensing: Creative Commons ShareAlike 4.0 International - https://creativecommons.org/licenses/by-sa/4.0
